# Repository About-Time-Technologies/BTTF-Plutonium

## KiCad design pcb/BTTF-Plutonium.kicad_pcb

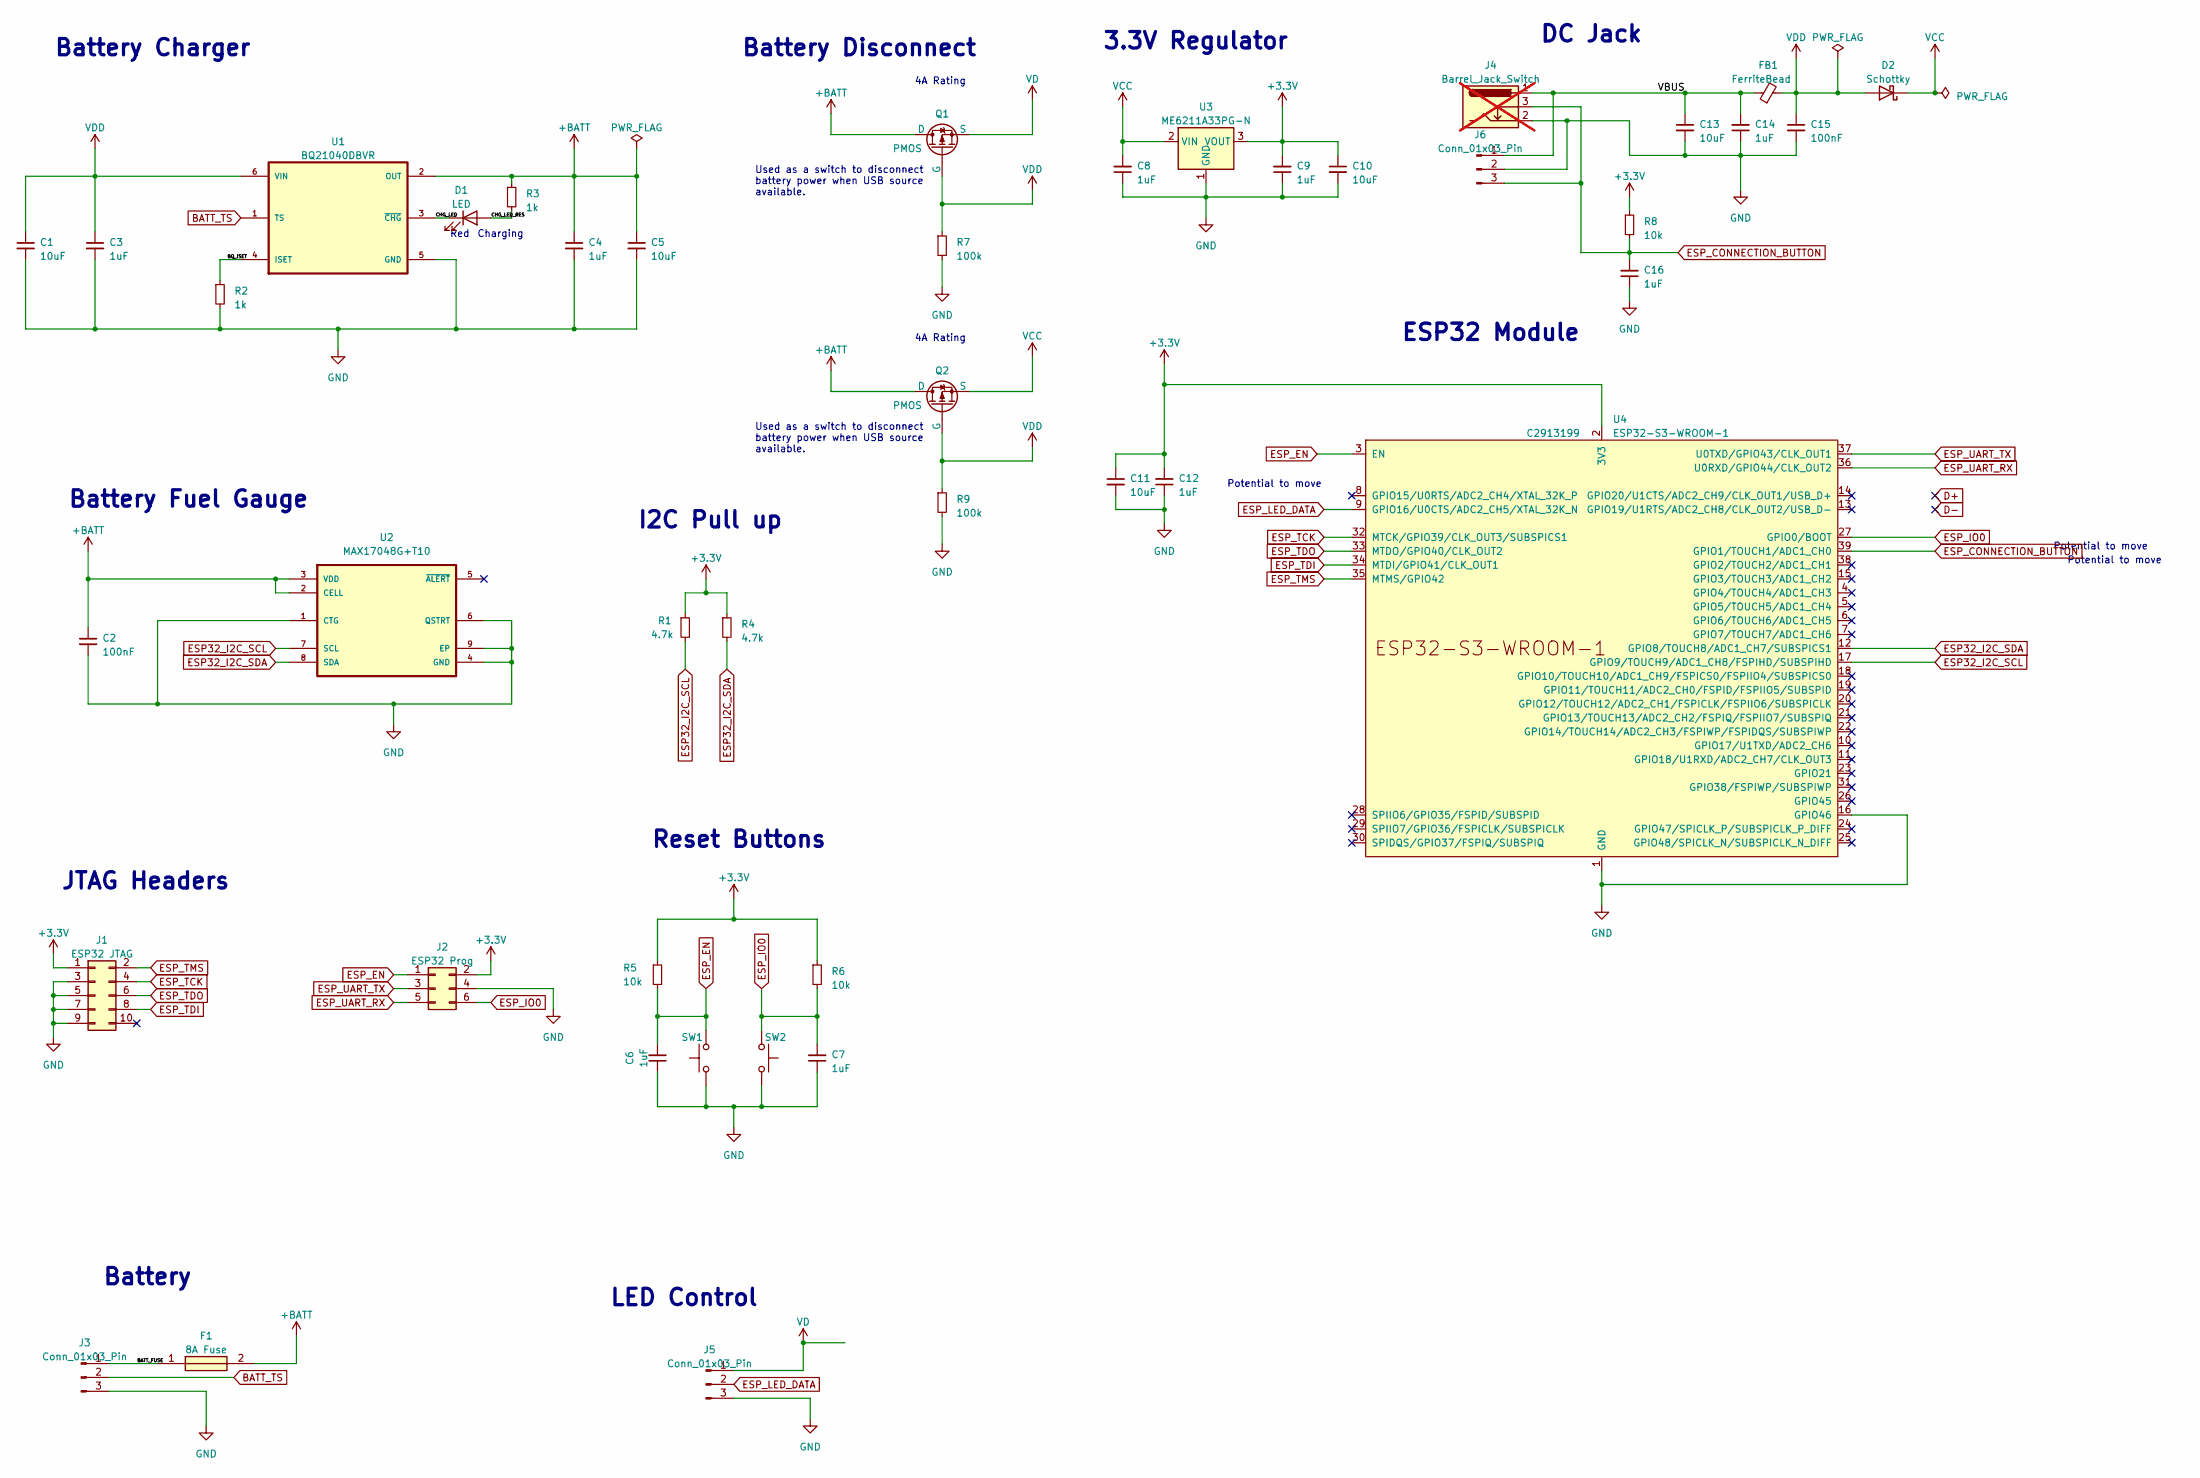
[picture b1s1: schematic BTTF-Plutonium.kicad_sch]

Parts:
C1, C5, C10, C11, C13: 10uF; C_0603_1608Metric; LCSC C19702
C2, C15: 100nF; C_0402_1005Metric; LCSC C1525
C3, C4, C6, C7, C8, C9, C12, C14, C16: 1uF; C_0402_1005Metric; LCSC C52923
D1: LED; LED_0603_1608Metric; LCSC C84256
D2: Schottky; D_SMA; LCSC C22452
F1: 8A Fuse; 0154008DR; Mouser Part Number 576-0154008.DR
FB1: FerriteBead; D_0805_2012Metric; LCSC C1015
J1: ESP32 JTAG; Tag-Connect_TC2050-IDC-NL_2x05_P1.27mm_Vertical_with_bottom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
J2: ESP32 Prog; Tag-Connect_TC2030-IDC-NL_2x03_P1.27mm_Vertical
J3, J5, J6: Conn_01x03_Pin; PinHeader_1x03_P2.54mm_Vertical
J4: Barrel_Jack_Switch; not fitted
Q1, Q2: PMOS; SSOP-8_3.9x5.05mm_P1.27mm; LCSC C235530
R1, R4: 4.7k; R_0402_1005Metric; LCSC C25900
R2: 1k; R_0603_1608Metric; LCSC C11702
R3: 1k; R_0603_1608Metric; LCSC C21190
R5, R6, R8: 10k; R_0603_1608Metric; LCSC C25744
R7, R9: 100k; R_0603_1608Metric; LCSC C25803
SW1, SW2: SW_Push; Small Push Button; LCSC C318884
U1: BQ21040DBVR; SOT95P280X145-6N; LCSC C202311
U2: MAX17048G+T10; SON50P200X200X80-9N; LCSC C2682616
U3: ME6211A33PG-N; SOT-89-3; LCSC C236673
U4: ESP32-S3-WROOM-1; ESP32-S3-WROOM-1U; LCSC C2913199

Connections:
+3.3V: C9.2, C10.1, C11.1, C12.2, J1.1, J2.2, R1.1, R4.1, R5.1, R6.1, R8.1, U3.3 (VOUT), U4.2 (3V3)
+BATT: C2.1, C4.1, C5.1, F1.2, Q1.5 (D), Q1.6 (D), Q1.7 (D), Q1.8 (D), Q2.5 (D), Q2.6 (D), Q2.7 (D), Q2.8 (D), R3.1, U1.2 (OUT), U2.2 (CELL), U2.3 (VDD)
/BATT_FUSE: F1.1, J3.1
/BQ_ISET: R2.1, U1.4 (ISET)
/CHG_LED: D1.1 (K), U1.3 (~CHG)
/CHG_LED_RES: D1.2 (A), R3.2
/VBUS: C13.1, C14.2, FB1.1, J6.1
BATT_TS: J3.2, U1.1 (TS)
ESP32_I2C_SCL: R1.2, U2.7 (SCL), U4.17 (GPIO9/TOUCH9/ADC1_CH8/FSPIHD/SUBSPIHD)
ESP32_I2C_SDA: R4.2, U2.8 (SDA), U4.12 (GPIO8/TOUCH8/ADC1_CH7/SUBSPICS1)
ESP_CONNECTION_BUTTON: C16.2, J6.3, R8.2, U4.39 (GPIO1/TOUCH1/ADC1_CH0)
ESP_EN: C6.2, J2.1, R5.2, SW1.2, U4.3 (EN)
ESP_IO0: C7.2, J2.6, R6.2, SW2.1, U4.27 (GPIO0/BOOT)
ESP_LED_DATA: J5.2, U4.9 (GPIO16/U0CTS/ADC2_CH5/XTAL_32K_N)
ESP_TCK: J1.4, U4.32 (MTCK/GPIO39/CLK_OUT3/SUBSPICS1)
ESP_TDI: J1.8, U4.34 (MTDI/GPIO41/CLK_OUT1)
ESP_TDO: J1.6, U4.33 (MTDO/GPIO40/CLK_OUT2)
ESP_TMS: J1.2, U4.35 (MTMS/GPIO42)
ESP_UART_RX: J2.5, U4.36 (U0RXD/GPIO44/CLK_OUT2)
ESP_UART_TX: J2.3, U4.37 (U0TXD/GPIO43/CLK_OUT1)
GND: C1.2, C2.2, C3.2, C4.2, C5.2, C6.1, C7.1, C8.1, C9.1, C10.2, C11.2, C12.1, C13.2, C14.1, C15.2, C16.1, J1.3, J1.5, J1.7, J1.9, J2.4, J3.3, J5.3, J6.2, R2.2, R7.2, R9.2, SW1.1, SW2.2, U1.5 (GND), U2.1 (CTG), U2.4 (GND), U2.6 (QSTRT), U2.9 (EP), U3.1 (GND), U4.1 (GND), U4.16 (GPIO46), U4.40 (GND), U4.41 (GND)
VCC: C8.2, D2.1 (K), Q2.1 (S), Q2.2 (S), Q2.3 (S), U3.2 (VIN)
VD: J5.1, Q1.1 (S), Q1.2 (S), Q1.3 (S)
VDD: C1.1, C3.1, C15.1, D2.2 (A), FB1.2, Q1.4 (G), Q2.4 (G), R7.1, R9.1, U1.6 (VIN)

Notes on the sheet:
JTAG Headers
Battery Fuel Gauge
Reset Buttons
Red
LED Control
DC Jack
4A Rating
3.3V Regulator
Battery Disconnect
Potential to move
Used as a switch to disconnect battery power when USB source available.
Charging
Battery Charger
Battery
ESP32 Module
I2C Pull up

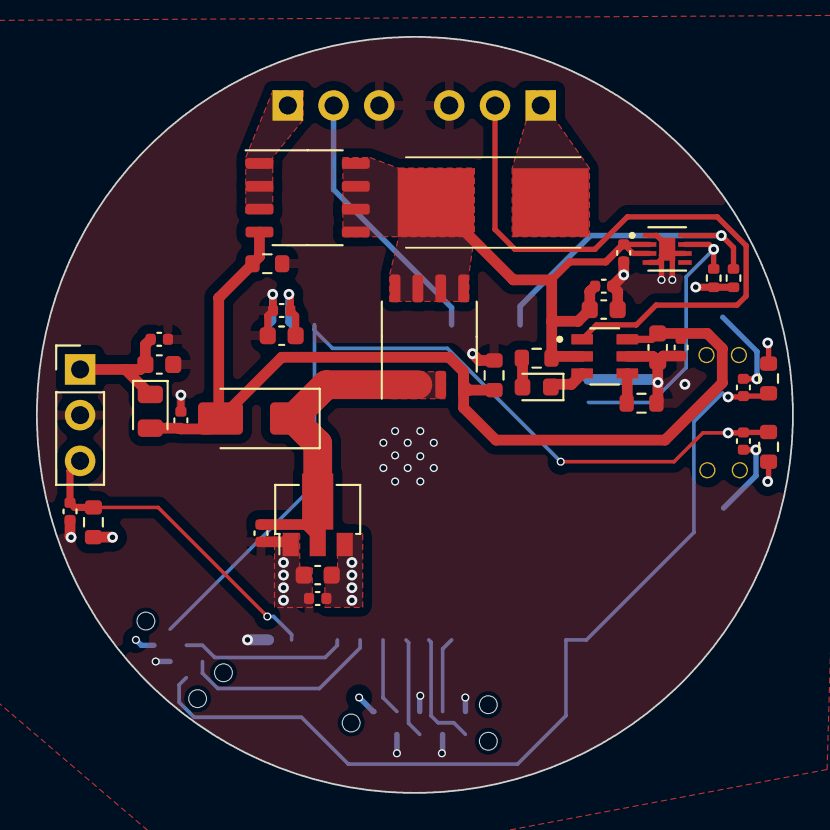
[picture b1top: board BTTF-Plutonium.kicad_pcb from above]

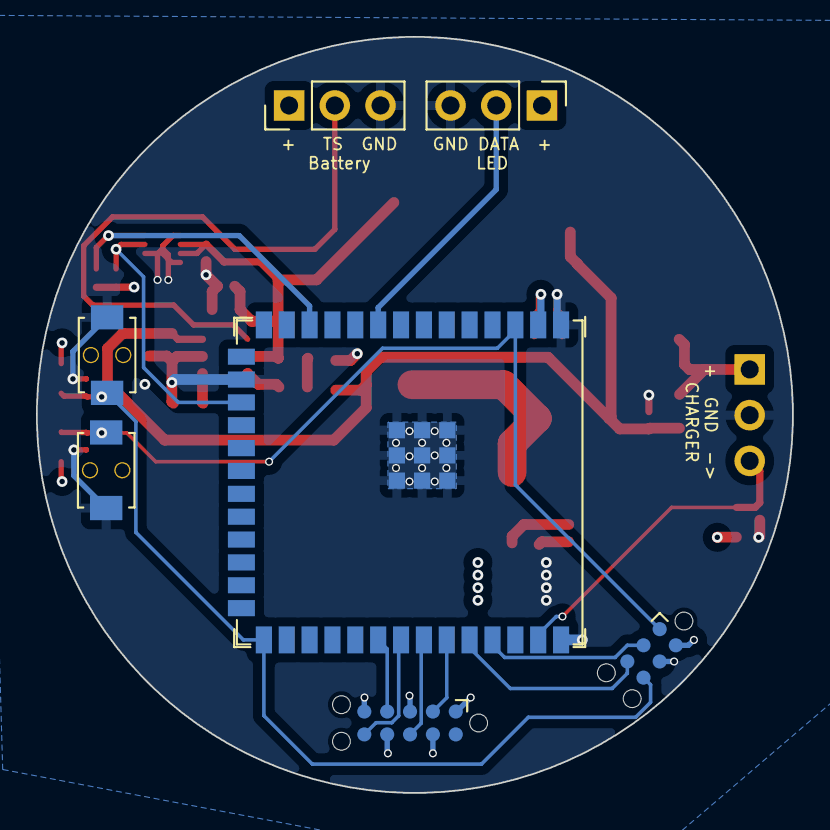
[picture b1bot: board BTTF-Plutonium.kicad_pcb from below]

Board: 4 copper layers, 42.0 x 42.0 mm, 42 parts (7 on the bottom side), 24 nets.

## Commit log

2023-09-16 Initial plutonium PCB
2023-09-17 Tidy up plutonium
2023-09-22 Moving bits around
2023-09-22 Blank slate
2023-09-22 Part placement
2023-09-24 Routing complete, new switch needed
